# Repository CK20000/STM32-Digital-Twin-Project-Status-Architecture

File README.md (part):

# KiCAD PCB Digital Twin - Plugin — Project Status & Architecture

https://github.com/user-attachments/assets/57d7ef48-a6f0-49e4-94a5-dc855cec5e4c

---

## PROJECT OVERVIEW

for easy managing I have organized the source files, but if you ever want to run this exact example versions, you need to have all the files in the root directory !!!

A closed-loop digital twin that bridges:

- KiCad PCB design       -> hardware definition (topology + geometry + values)
- STM32F407VETx firmware -> control logic (compiled to .elf)
- Renode                 -> cycle-accurate virtual MCU execution
- Python + ZeroMQ        -> message-passing middleware
- ngspice                -> real analog circuit simulation (auto-generated)
- PyQt6 control panel    -> live external analog + digital input injection
- PyQt6 unified UI       -> all 7 viewers + control panel + pipeline in one window
- matplotlib             -> live PCB visualization with physics overlays

**Key achievement:** Zero hardcoded circuit knowledge, zero faked inputs.
Every number on screen traces from a real KiCad component through real
firmware through real SPICE. Every panel input travels through Renode's
memory bus and into the SPICE netlist, exactly like a real external signal.

https://github.com/user-attachments/assets/5415f41c-1950-47eb-a591-bcc1c15813ef

https://github.com/user-attachments/assets/28cafe8e-76d3-48ea-92d0-15f687ff5b82

https://github.com/user-attachments/assets/54334765-b6d6-46bb-97e2-3d35a90c9ced

https://github.com/user-attachments/assets/97b0375e-3175-4ab2-a4fb-0aa53eb2be76

https://github.com/user-attachments/assets/55057f72-92d3-42ab-a68e-e2e90e522510

Full data path:

```text
KiCad (.kicad_pcb) --+-- digital_twin_netlist.json  (electrical topology)
                     |
                     +-- pcb_geometry.json          (visual geometry)
                     |
                     v
                netlist_analyzer.py  --> component_classification.json
                     |
                     v
                spice_compiler.py    --> auto_generated.cir
                                         + source_metadata.json
                     |
                     v
                inject_trace_resistance.py
                     |
                     v
                auto_generated_with_traces.cir

STM32 Firmware (C) --> automation_plc.elf
                            |
                    Renode (virtual STM32F407)
                            |
                    +-------+--------+
                    |                |
              monitor tcp:1234   UARTs tcp:12345/12346
                    |                |
                    v                v
        renode_reader.py       stm32_bridge.py
        (owns monitor)         (RS485 + ESP)
                    |                |
        ZMQ PUB:5557 (OBS)      ZMQ PUB:5555
        ZMQ SUB:5558 (INJECT)       |
                    |               v
                    |          test_sub.py
                    |
        +-----------+--------------+
        |                          |
        v                          v
pyspice_solver.py            pyqt6_control.py
(OBS:5557 in)                (INJECT:5558 out)
(replaces V_* values)        (8 analog sliders)
        |                    (8 digital checkboxes)
        |                          |
   auto_generated_with_traces.cir |
        |                          |
   ngspice subprocess <------------+
        |
   ZMQ PUB:5556
   (SIM / RAIL / RAIL_I / POWER / CURRENT / LOAD_I / LED_I / PIN / NODE / DOUT)
        |
        +---------+---------+---------+---------+---------+---------+
        |         |         |         |         |         |         |
        v         v         v         v         v         v         v
    pcb_      pcb_      pcb_      pcb_      pcb_      pcb_      board_
    viewer    resist    current   voltage   heat      thermal   thermal
    (LEDs)    (R)       (I)       (V)       (P)       (Tj)      field_v2
```

## GOAL TRACKER

| #  | Goal                                                       | Status   |
|----|------------------------------------------------------------|----------|
| 1  | Live PCB overlay with animated LED states                  | DONE     |
| 2A | Trace resistance extraction + physics modeling             | DONE     |
| 2B | Current flow visualization on traces                       | DONE     |
| 2C | Power dissipation heat map (per component)                 | DONE     |
| 2D | Thermal simulation — per-component θja + 2D diffusion field| DONE     |
| 3  | Board health pre-check (rails, loads, overtemperature)     | DONE     |
| -- | Auto-generated SPICE compiler (unplanned bonus)            | DONE     |
| -- | Trace resistance injected into SPICE netlist               | DONE     |
| -- | Auto-generated source metadata (no hardcoded nets)         | DONE     |
| -- | Renode memory reader (replaces UART as firmware source)    | DONE     |
| -- | Bidirectional Python → Renode injection                    | DONE     |
| -- | External analog input control panel (PyQt6)                | DONE     |
| -- | External digital input control panel (PyQt6)               | DONE     |
| -- | Voltage viewer (per-net DC node voltages)                  | DONE     |
| -- | Digital-output "armed" state outline on current viewer     | DONE     |
| -- | Unified PyQt6 dashboard (tabs + sidebar + pipeline grid)   | DONE     |

---

## WHAT HAS BEEN ACHIEVED

### Foundation Layer

| Milestone                                                     | Status | Verified By                     |
|---------------------------------------------------------------|--------|---------------------------------|
| Hardware schematic review (ESP-12F, MAX3485, LM358, etc.)     | Done   | Netlist inspection              |
| KiCad PCB netlist extraction to JSON                          | Done   | extraction.py                   |
| STM32CubeMX pinout configured for all peripherals             | Done   | .ioc file, CubeMX GUI           |
| ADC1 with DMA (8 channels, circular mode)                     | Done   | adc.c generated                 |
| TIM4 PWM (4 motor channels on PD12-PD15)                      | Done   | tim.c generated                 |
| USB OTG FS Device CDC                                         | Done   | usb_device.c generated          |
| Firmware compiled to automation_plc.elf                       | Done   | STM32CubeIDE build              |
| Renode virtual STM32F407 running firmware                     | Done   | plc_twin machine started        |
| UARTs exposed as TCP sockets                                  | Done   | Ports 12345, 12346              |
| Renode monitor exposed on TCP 1234                            | Done   | renode_reader.py                |
| Python bridge (UART -> ZeroMQ) with byte-level framing        | Done   | Live PLC_ALIVE packets          |
| Subscriber displaying live ADC values                         | Done   | Parsed 8-channel ADC arrays     |
| End-to-end pipeline running continuously                      | Done   | 190000+ packets streamed        |

### Firmware Observable Layer

| Milestone                                                     | Status | Verified By                     |
|---------------------------------------------------------------|--------|---------------------------------|
| get_symbols.py parses linker .map for `obs_*`/`in_*` symbols  | Done   | symbols.json                    |
| renode_reader.py owns Renode monitor (single client on 1234)  | Done   | Live OBS stream                 |
| Batched contiguous-span read (1 monitor cmd per cycle)        | Done   | Fast polling                    |
| Publishes OBS:<name>:<hex> on ZMQ 5557                        | Done   | Subscribed by solver + panel    |
| Subscribes INJECT:<name>:<value> on ZMQ 5558                  | Done   | Writes via sysbus WriteWord     |
| Coalesces rapid injections (latest value wins per cycle)      | Done   | Slider drags don't flood        |
| Skips no-op writes (last_written cache)                       | Done   | Monitor stays clean             |
| Auto-reconnect on Renode monitor drop                         | Done   | Recovers from Renode restart    |
| renode_cmd.py one-shot monitor command tool                   | Done   | Manual debugging                |
| Digital inputs IE8..IE15 injectable via INJECT path            | Done   | 5000 mV → 5 V field voltage      |
| Digital outputs E0..E7, D12..D15 exposed for state display     | Done   | DOUT topic on ZMQ 5556           |

### Simulation Layer

| Milestone                                                     | Status | Verified By                     |
|---------------------------------------------------------------|--------|---------------------------------|
| Netlist analyzer — auto-classifies 143 components             | Done   | netlist_analyzer.py             |
| SPICE compiler — auto-generates netlist from KiCad data       | Done   | spice_compiler.py               |
| Source metadata emitter (SPICE branch <-> KiCad net)          | Done   | source_metadata.json            |
| STM32 self-load (50 mA) + ESP-12F load (80 mA) modeled        | Done   | Verified in ngspice output      |
| LDO + buck regulator models with upstream current reflection  | Done   | Voltage rails consistent        |
| Trace resistance (I²R losses over copper)                     | Done   | trace_resistance.py             |
| Trace resistance injected into SPICE between pads             | Done   | auto_generated_with_traces.cir  |
| Per-component SPICE power parsing (R, I, D elements)          | Done   | ngspice POWER topic             |
| Per-resistor current parsing (R_pd_E8..E15 pin currents)      | Done   | CURRENT:E8..E15 topic           |
| Behavioral optocoupler models (PC817, 6N137)                  | Done   | optocoupler.lib                 |
| Live solver with per-packet netlist rewriting                 | Done   | pyspice_solver.py               |
| OBS-driven value substitution (no UART dependency)            | Done   | Solved from renode_reader       |
| Per-net node voltages published as NODE:<net>:<volts>         | Done   | Voltage viewer                  |
| Digital-output state published as DOUT:<net>:<0/1>            | Done   | Current viewer "armed" outline  |

### External Control Layer

| Milestone                                                     | Status | Verified By                     |
|---------------------------------------------------------------|--------|---------------------------------|
| channels.json maps user channels → in_* → obs_*               | Done   | 8 analog + 8 digital entries    |
| pyqt6_control.py — analog sliders (0–10 V, 20 Hz flush)       | Done   | Verified live                   |
| pyqt6_control.py — digital checkboxes (IE8..IE15, 5 V ON)     | Done   | Verified live                   |
| Reads OBS back into panel to confirm injection landed         | Done   | obs label updates on slider move|
| input_injector.py — standalone CLI injector                   | Done   | Reference tool                  |
| Digital input: opto LED current ~10.6 mA when ON              | Done   | CURRENT:/f4/IO/IExx             |
| Digital input: MCU pin current ~0.33 mA through pull-down     | Done   | CURRENT:Exx                     |
| Upstream LDO reflects opto output load (~1.4 mA on 3v3-LDO1)  | Done   | RAIL_I:3v3-LDO1                 |
| Panel embedded into unified dashboard sidebar (live)          | Done   | No changes to pyqt6_control.py  |

### Visualization Layer

| Milestone                                                     | Status | Verified By                     |
|---------------------------------------------------------------|--------|---------------------------------|
| Automated PCB top-view renderer (no manual export)            | Done   | pcb_render.py                   |
| Copper trace + pad + body + silkscreen extraction             | Done   | pcb_geometry.json               |
| Rotation-aware pad rendering (fixes QFP at 45°)               | Done   | U5 verified                     |
| F.Fab chain-lines-to-polygon for component bodies             | Done   | All passives render correctly   |
| Performance optimization (PatchCollection / LineCollection)   | Done   | ~1700 artists → ~10 artists     |
| Live LED overlay (7 LEDs: D3-D9)                              | Done   | pcb_viewer.py                   |
| Trace resistance view with hover inspect                      | Done   | pcb_resistance_view.py          |
| Current flow view (colored traces on top layer)               | Done   | pcb_current_view.py             |
| Power dissipation heat map (log + linear + jet)               | Done   | pcb_heat_view.py                |
| Per-component thermal view (θja model)                        | Done   | pcb_thermal_view.py             |
| 2D thermal field v1 (single-layer k_eff)                      | Done   | pcb_thermal_field.py            |
| 2D thermal field v2 (2-layer copper + vias + FR4)             | Done   | pcb_thermal_field_v2.py         |
| Bounding-box hover detection for large components             | Done   | Fixed for U4/U5                 |
| Voltage view (per-net DC voltage, viridis 0–12 V)             | Done   | pcb_voltage_view.py             |
| Digital-output outline (amber=ARMED, slate=IDLE)              | Done   | pcb_current_view.py             |
| Resistance viewer info panel visible at startup               | Done   | pcb_resistance_view.py          |
| Unified dashboard — 7 tabs + sidebar + pipeline grid          | Done   | dashboard_unified.py            |

### Automation Layer (Goal 3)

| Milestone                                                     | Status | Verified By                     |
|---------------------------------------------------------------|--------|---------------------------------|
| Board health monitor (12-test battery)                        | Done   | board_health.py                 |
| Rail voltage tolerance check (±5%)                            | Done   | All 4 rails PASS                |
| Load current plausibility check                               | Done   | STM32 + ESP PASS                |
| Total power budget check                                      | Done   | <2 W threshold                  |
| Over-temperature prediction (θja model)                       | Done   | Peak 38.1 °C at U4              |
| Short-circuit detection (rail current > 1 A)                  | Done   | Max 144.7 mA                    |
| SIM packet freshness check                                    | Done   | <5 s stale threshold            |
| ADC channel-set verification                                  | Done   | 4/4 SIM fields present          |
| ESP packet rate monitor (rolling window)                      | Done   | 4-6 Hz observed                 |
| Single-shot mode with exit code (`--once`)                    | Done   | CI-friendly                     |

---

## PROJECT FILE INVENTORY

### Core Pipeline Files

| File                | Language      | Purpose                                                                  |
|---------------------|---------------|--------------------------------------------------------------------------|
| run_core.bat        | Batch         | Pre-flight + launches Renode, bridge, reader, solver, subscriber        |
| run_unified_dashboard.bat | Batch   | Launches the unified dashboard; pipeline starts inside as tabs          |
| run_led_viewer.bat  | Batch         | Opens pcb_viewer.py                                                     |
| run_current_viewer.bat | Batch      | Opens pcb_current_view.py                                               |
| run_voltage_viewer.bat | Batch    | Opens pcb_voltage_view.py standalone                                     |
| run_resistance_viewer.bat | Batch    | Opens pcb_resistance_view.py                                            |
| run_heat_viewer.bat | Batch         | Opens pcb_heat_view.py                                                  |
| run_thermal_viewer.bat | Batch      | Opens pcb_thermal_field_v2.py                                           |
| run_health.bat      | Batch         | Continuous health monitor                                               |
| run_health_once.bat | Batch         | Single-shot health check with exit code                                 |
| rebuild_spice.bat   | Batch         | Regenerates classification → SPICE → trace injection                    |
| rebuild_geometry.bat| Batch         | Two-step geometry regeneration (KiCad Python + system Python)           |
| stop_all.bat        | Batch         | Kills Renode, ngspice, and project Python processes                     |
| machine.resc        | Renode script | Defines virtual STM32F407, loads .elf, exposes UARTs                    |
| stm32_bridge.py     | Python        | Reads TCP UART streams, publishes RS485/ESP to ZMQ 5555                 |
| renode_reader.py    | Python        | Owns Renode monitor 1234, reads obs_*, writes in_*, ZMQ 5557/5558       |
| get_symbols.py      | Python        | Parses linker .map → symbols.json (obs_* and in_* addresses)            |
| input_injector.py   | Python        | Standalone INJECT publisher (reference tool)                            |
| renode_cmd.py       | Python        | One-shot Renode monitor command tool                                    |
| pyspice_solver.py   | Python        | Loads netlist, substitutes OBS values, calls ngspice, publishes 5556    |
| pyqt6_control.py    | Python        | External control panel (8 analog sliders + 8 digital checkboxes)        |
| dashboard_unified.py| Python        | All-in-one PyQt6 dashboard (7 viewer tabs + sidebar + pipeline grid)     |
| test_sub.py         | Python        | Subscribes to all ZMQ topics and displays live text data                |

### Auto-SPICE Compiler Files

| File                            | Purpose                                                        |
|---------------------------------|----------------------------------------------------------------|
| netlist_analyzer.py             | Classifies every component (R, C, LED, LDO, MCU, etc.)         |
| component_classification.json   | Output: type + value + nets per refdes                         |
| spice_compiler.py               | Generates complete SPICE netlist + source metadata             |
| auto_generated.cir              | Generated SPICE netlist (143 components + rails + loads)       |
| source_metadata.json            | Maps SPICE branch names to KiCad nets (no hardcoding)          |
| inject_trace_resistance.py      | Injects R_trace elements between regulator and load            |
| auto_generated_with_traces.cir  | Final netlist — this is what the solver loads                  |
| optocoupler.lib                 | Behavioral SPICE subcircuits for PC817 and 6N137               |

### Hardware / Physics Files

| File                          | Purpose                                                       |
|-------------------------------|---------------------------------------------------------------|
| automation.kicad_pcb          | KiCad PCB layout (source of truth)                            |
| automation.kicad_pro          | KiCad project file                                            |
| automation.kicad_sch          | KiCad main schematic                                          |
| A_IN.kicad_sch                | Analog input schematic sheet                                  |
| IO.kicad_sch                  | Industrial I/O schematic sheet                                |
| MOTORS.kicad_sch              | Motor driver schematic sheet                                  |
| DEBUG.kicad_sch               | Debug/LED schematic sheet                                     |
| f4.kicad_sch                  | STM32F407 core schematic sheet                                |
| digital_twin_netlist.json     | Extracted net topology (component, value, pin, net)           |
| extraction.py                 | pcbnew script that generates the JSON netlist from the PCB    |
| trace_resistance.py           | Computes DC resistance per trace + per net                    |
| net_resistance.json           | Output: resistance topology                                   |
| automation_plc.ioc            | STM32CubeMX project configuration                             |

### Visualization Files

| File                     | Language  | Purpose                                                              |
|--------------------------|-----------|----------------------------------------------------------------------|
| pcb_extract_geometry.py  | Python    | Reads .kicad_pcb via pcbnew, dumps geometry to JSON                  |
| pcb_geometry.json        | JSON      | Tracks, vias, footprints, pads, F.Fab, F.SilkS                       |
| pcb_render.py            | Python    | Renders pcb_background.png                                           |
| pcb_render_meta.json     | JSON      | Pixel <-> mm coordinate mapping                                      |
| pcb_background.png       | PNG       | Static PCB top-view render                                           |
| pcb_viewer.py            | Python    | Live LED overlay (Goal 1)                                            |
| pcb_resistance_view.py   | Python    | Trace resistance view with hover                                     |
| pcb_current_view.py      | Python    | Current flow view (colored traces on top)                            |
| pcb_voltage_view.py      | Python    | Per-net DC voltage view (live from ngspice NODE topic)               |
| pcb_heat_view.py         | Python    | Power dissipation heat map                                           |
| pcb_thermal_view.py      | Python    | Per-component θja thermal view                                       |
| pcb_thermal_field.py     | Python    | 2D thermal diffusion (single-layer k_eff)                            |
| pcb_thermal_field_v2.py  | Python    | 2D thermal diffusion (2-layer copper + vias + FR4)                   |

### Configuration Files

| File              | Purpose                                                       |
|-------------------|---------------------------------------------------------------|
| channels.json     | Channel map: id → in_* symbol → obs_* observable → kind       |
| symbols.json      | Address + size of every obs_* and in_* firmware variable      |

### Automation Files

| File              | Purpose                                                    |
|-------------------|------------------------------------------------------------|
| board_health.py   | 12-test battery, continuous or --once mode                 |

### Firmware Files

| File                                 | Purpose                                              |
|--------------------------------------|------------------------------------------------------|
| firmware/Debug/automation_plc.elf    | Compiled firmware (used by Renode)                   |
| firmware/Core/Src/main.c             | Main application (injection copy loop + LED bitmask) |
| firmware/Core/Src/adc.c              | ADC1 + DMA initialization                            |
| firmware/Core/Src/dac.c              | DAC1/DAC2 initialization                             |
| firmware/Core/Src/tim.c              | TIM4 PWM initialization                              |
| firmware/Core/Src/usart.c            | USART2, USART3 initialization                        |
| firmware/Core/Src/spi.c              | SPI1, SPI2 initialization                            |
| firmware/Core/Src/i2c.c              | I2C1 initialization                                  |
| firmware/Core/Src/gpio.c             | GPIO init                                            |
| firmware/Core/Src/dma.c              | DMA controller initialization                        |
| firmware/Core/Src/usb_device.c       | USB CDC device setup                                 |
| firmware/automation_plc.ioc          | CubeMX project (used for regeneration)               |

### External Dependencies

| Dependency     | Version    | Purpose                                                              |
|----------------|------------|----------------------------------------------------------------------|
| STM32CubeMX    | (latest)   | Pin/peripheral configurator                                          |
| STM32CubeIDE   | (latest)   | Compiler + debugger                                                  |
| Renode         | (latest)   | Virtual MCU execution                                                |
| ngspice        | 47         | Analog circuit simulator (C:\Users\user\Downloads\Spice64\bin\ngspice_con.exe) |
| Python (system)| 3.10+      | All pipeline scripts + viewers                                       |
| Python (KiCad) | 3.x        | Only used for pcbnew scripts (extraction)                            |
| pyzmq          | latest     | ZeroMQ bindings                                                      |
| matplotlib     | latest     | All rendering + live viewers                                         |
| scipy          | latest     | Sparse solver for 2D thermal diffusion                               |
| PyQt6          | latest     | External control panel GUI + unified dashboard                       |

---

## STM32F407VETx PINOUT (FINAL)

| Peripheral              | Pin                | Function                    | Notes                          |
|-------------------------|--------------------|-----------------------------|--------------------------------|
| HSE Crystal             | PH0, PH1           | RCC_OSC_IN/OUT              | 8 MHz                          |
| Debug                   | PA13, PA14         | SWDIO, SWCLK                | Serial Wire mode               |
| ESP-12F                 | PB10, PB11         | USART3_TX/RX                | 115200 8N1                     |
| MAX3485 (RS-485)        | PA2, PA3, PD11     | USART2_TX/RX, DE/RE         | Direction control on PD11      |
| W25Q128 (SPI Flash)     | PB3, PB4, PB5, PD6 | SPI1_SCK/MISO/MOSI, CS      | CS on PD6                      |
| USB-C                   | PA11, PA12         | USB_DM, USB_DP              | Full Speed Device              |
| Motor PWM               | PD12-PD15          | TIM4_CH1-CH4                | 4 channels                     |
| Debug LEDs              | PC10, PC11, PC12, PA15 | GPIO_Output             |                                |
| I2C Expansion           | PB6, PB7           | I2C1_SCL/SDA                |                                |
| Analog In 1-4           | PC0-PC3            | ADC1_IN10-13                | 0-10V via 10k/4.7k divider     |
| Analog In 5-6           | PC4, PC5           | ADC1_IN14-15                | Same divider                   |
| Analog In 7-8           | PB0, PB1           | ADC1_IN8-9                  | Same divider                   |
| Analog Out 1-2          | PA4, PA5           | DAC_OUT1/2                  | Via LM358 gain=3               |
| Digital Inputs 8-15     | PE8-PE15           | GPIO_Input                  | Opto-isolated (U31..U30)       |

ADC Rank Ordering (as configured in CubeMX):

    Rank 1: IN8  (PB0) -> adc_values[0]  -> A_IN7
    Rank 2: IN9  (PB1) -> adc_values[1]  -> A_IN8
    Rank 3: IN10 (PC0) -> adc_values[2]  -> A_IN1
    Rank 4: IN11 (PC1) -> adc_values[3]  -> A_IN2
    Rank 5: IN12 (PC2) -> adc_values[4]  -> A_IN3
    Rank 6: IN13 (PC3) -> adc_values[5]  -> A_IN4
    Rank 7: IN14 (PC4) -> adc_values[6]  -> A_IN5
    Rank 8: IN15 (PC5) -> adc_values[7]  -> A_IN6

---

## DATA PROTOCOLS

### Renode Observable Protocol (Renode → Python)

`renode_reader.py` reads a single contiguous span containing every
`obs_*` / `in_*` symbol and publishes each one:

    OBS:<symbol_name>:<hex_bytes>

Example:

    OBS:obs_v_in1:7f0f
    OBS:obs_v_ie8_drv:8813
    OBS:obs_v_d4_drv:00

Published on ZMQ **5557**.

### Renode Injection Protocol (Python → Renode)

Any subscriber publishes:

    INJECT:<symbol_name>:<uint16_value>

Example:

    INJECT:in_v_in1:3967
    INJECT:in_v_ie8_drv:5000

Published on ZMQ **5558**; `renode_reader.py` coalesces and writes via
`sysbus WriteWord` to the symbol's address.

### ESP UART Packet (Firmware → Bridge, legacy path)

- 20 bytes total
- [0xAA][0x55] — sync header
- 8 × 16-bit big-endian ADC values (bytes 2-17)
- 1 byte LED bitmask (byte 18)
- 1 byte reserved (byte 19)

### ZeroMQ Topics

| Topic                        | Port | Publisher      | Format                                    |
|------------------------------|------|----------------|-------------------------------------------|
| RS485:<hex>                  | 5555 | stm32_bridge   | Hex-encoded ASCII ("PLC_ALIVE\r\n")       |
| ESP:<hex>                    | 5555 | stm32_bridge   | Hex-encoded 20-byte ADC + LED packet      |
| OBS:<name>:<hex>             | 5557 | renode_reader  | Firmware observable raw bytes             |
| INJECT:<name>:<value>        | 5558 | any            | Write request to a firmware variable      |
| SIM:<n>:<key=val,...>        | 5556 | solver         | Simulation summary string                 |
| CURRENT:<net>:<amps>         | 5556 | solver         | Per-net current (auto-mapped + pin R's)   |
| POWER:<ref>:<watts>          | 5556 | solver         | Per-component power dissipation           |
| RAIL:<net>:<volts>           | 5556 | solver         | Power rail node voltages                  |
| RAIL_I:<net>:<amps>          | 5556 | solver         | Power rail delivered currents             |
| LED_I:<ref>:<amps>           | 5556 | solver         | LED drive currents                        |
| LOAD_I:<label>:<amps>        | 5556 | solver         | MCU / ESP self-load currents              |
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
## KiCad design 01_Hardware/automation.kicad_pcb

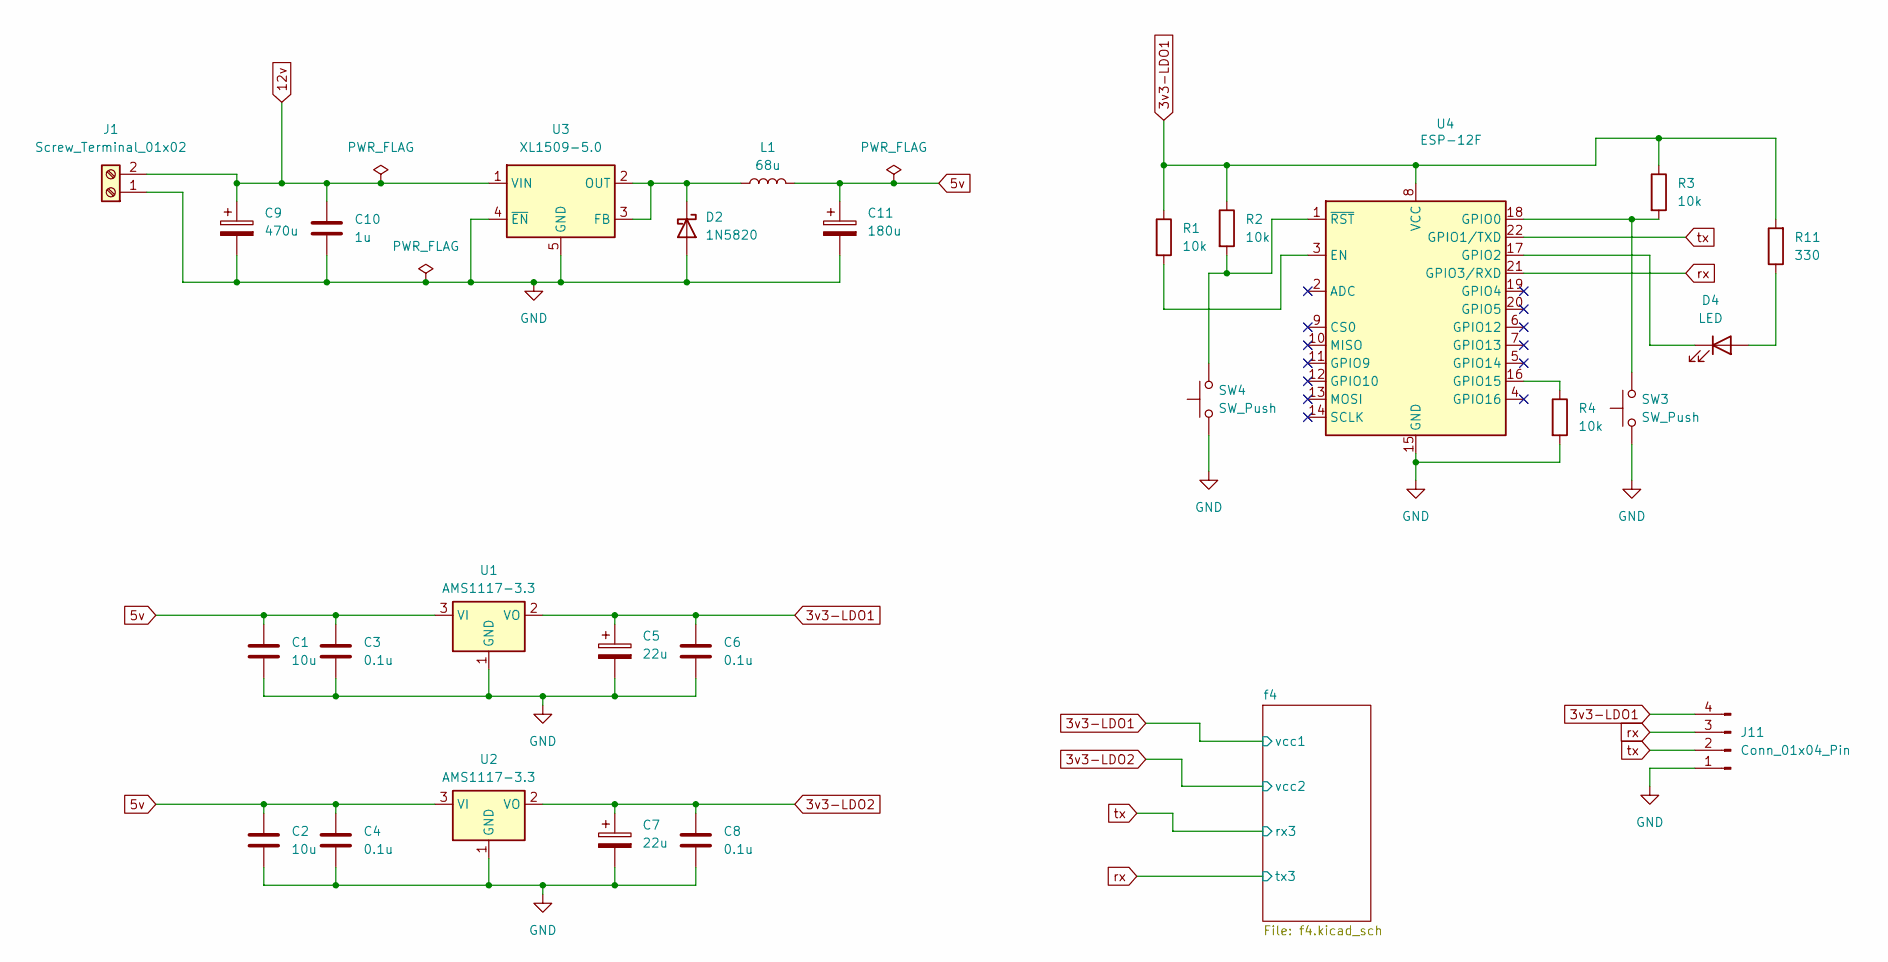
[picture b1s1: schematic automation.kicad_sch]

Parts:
C1, C2: 10u; C_0805_2012Metric_Pad1.18x1.45mm_HandSolder
C3, C4, C6, C8: 0.1u; C_0805_2012Metric_Pad1.18x1.45mm_HandSolder
C5, C7: 22u; C_0805_2012Metric_Pad1.18x1.45mm_HandSolder
C9: 470u; C_0805_2012Metric_Pad1.18x1.45mm_HandSolder
C10: 1u; C_0805_2012Metric_Pad1.18x1.45mm_HandSolder
C11: 180u; C_0805_2012Metric_Pad1.18x1.45mm_HandSolder
D2: 1N5820; D_1206_3216Metric_Pad1.42x1.75mm_HandSolder
D4: LED; LED_0805_2012Metric_Pad1.15x1.40mm_HandSolder
J1: Screw_Terminal_01x02; TerminalBlock_Phoenix_MKDS-1,5-2_1x02_P5.00mm_Horizontal
J11: Conn_01x04_Pin; PinHeader_1x04_P2.54mm_Vertical
L1: 68u; L_APV_ANR6020
R1, R2, R3, R4: 10k; R_0805_2012Metric_Pad1.20x1.40mm_HandSolder
R11: 330; R_0805_2012Metric_Pad1.20x1.40mm_HandSolder
SW3, SW4: SW_Push; SW_Push_SPST_NO_Alps_SKRK
U1, U2: AMS1117-3.3; SOT-223-3_TabPin2
U3: XL1509-5.0; SOIC-8_3.9x4.9mm_P1.27mm
U4: ESP-12F; ESP-12E

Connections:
3v3-LDO1: C5.1, C6.1, J11.4, R1.1, R2.1, R3.1, R11.2, U1.2 (VO), U4.8 (VCC); also elsewhere on the board
3v3-LDO2: C7.1, C8.1, U2.2 (VO); also elsewhere on the board
5v: C1.1, C2.1, C3.1, C4.1, C11.1, L1.2, U1.3 (VI), U2.3 (VI); also elsewhere on the board
12v: C9.1, C10.1, J1.2, U3.1 (VIN); also elsewhere on the board
GND: C1.2, C2.2, C3.2, C4.2, C5.2, C6.2, C7.2, C8.2, C9.2, C10.2, C11.2, D2.2 (A), J1.1, J11.1, R4.2, SW3.1, SW4.1, U1.1 (GND), U2.1 (GND), U3.4 (~EN), U3.5 (GND), U3.6 (GND), U3.7 (GND), U3.8 (GND), U4.15 (GND); also elsewhere on the board
unnamed: D2.1 (K), L1.1, U3.2 (OUT), U3.3 (FB)
unnamed: D4.2 (A), R11.1
unnamed: D4.1 (K), U4.17 (GPIO2)
unnamed: R1.2, U4.3 (EN)
unnamed: R3.2, SW3.2, U4.18 (GPIO0)
unnamed: R4.1, U4.16 (GPIO15)
unnamed: R2.2, SW4.2, U4.1 (~RST)
rx: J11.3, U4.21 (GPIO3/RXD); also elsewhere on the board
tx: J11.2, U4.22 (GPIO1/TXD); also elsewhere on the board

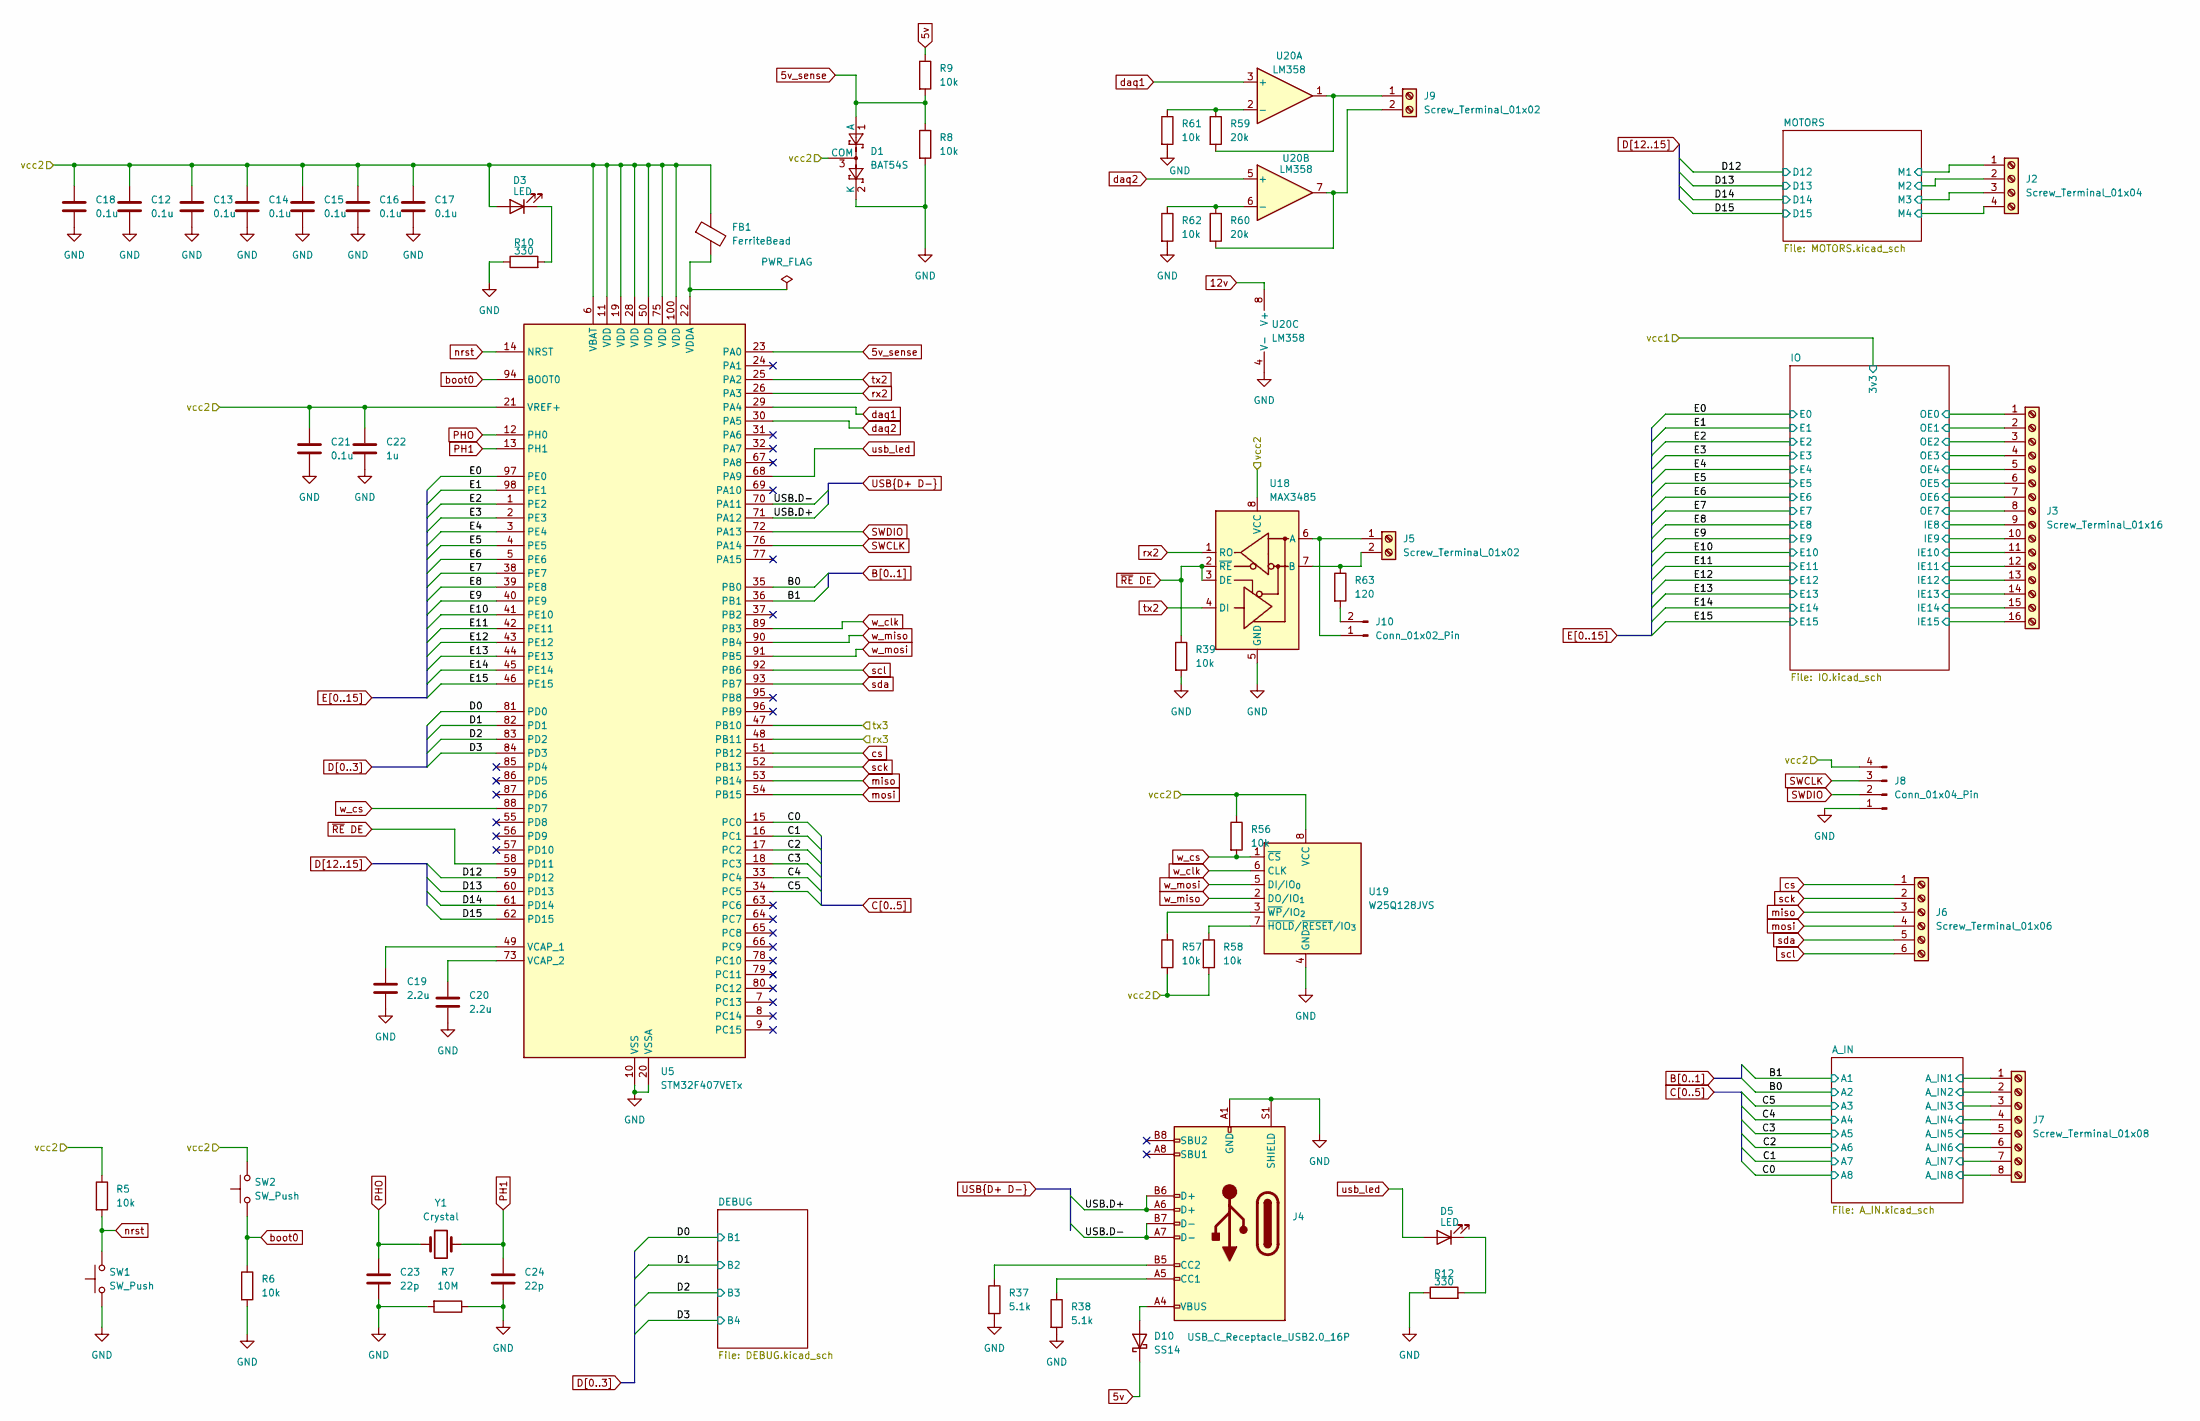
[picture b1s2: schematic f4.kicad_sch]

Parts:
C12, C13, C14, C15, C16, C17, C18, C21: 0.1u; C_0805_2012Metric_Pad1.18x1.45mm_HandSolder
C19, C20: 2.2u; C_0805_2012Metric_Pad1.18x1.45mm_HandSolder
C22: 1u; C_0805_2012Metric_Pad1.18x1.45mm_HandSolder
C23, C24: 22p; C_0805_2012Metric_Pad1.18x1.45mm_HandSolder
D1: BAT54S; SOT-23
D3, D5: LED; LED_0805_2012Metric_Pad1.15x1.40mm_HandSolder
D10: SS14; D_SMA
FB1: FerriteBead; L_1206_3216Metric_Pad1.22x1.90mm_HandSolder
J2: Screw_Terminal_01x04; TerminalBlock_Phoenix_MKDS-1,5-4_1x04_P5.00mm_Horizontal
J3: Screw_Terminal_01x16; TerminalBlock_Phoenix_MKDS-1,5-16_1x16_P5.00mm_Horizontal
J4: USB_C_Receptacle_USB2.0_16P; USB_C_Receptacle_GCT_USB4105-xx-A_16P_TopMnt_Horizontal
J5, J9: Screw_Terminal_01x02; TerminalBlock_Phoenix_MKDS-1,5-2_1x02_P5.00mm_Horizontal
J6: Screw_Terminal_01x06; TerminalBlock_Phoenix_MKDS-1,5-6_1x06_P5.00mm_Horizontal
J7: Screw_Terminal_01x08; TerminalBlock_Phoenix_MKDS-1,5-8_1x08_P5.00mm_Horizontal
J8: Conn_01x04_Pin; PinHeader_1x04_P2.54mm_Vertical
J10: Conn_01x02_Pin; PinHeader_1x02_P2.54mm_Vertical
R5, R6, R8, R9, R39, R56, R57, R58, R61, R62: 10k; R_0805_2012Metric_Pad1.20x1.40mm_HandSolder
R7: 10M; R_0805_2012Metric_Pad1.20x1.40mm_HandSolder
R10, R12: 330; R_0805_2012Metric_Pad1.20x1.40mm_HandSolder
R37, R38: 5.1k; R_0805_2012Metric_Pad1.20x1.40mm_HandSolder
R59, R60: 20k; R_0805_2012Metric_Pad1.20x1.40mm_HandSolder
R63: 120; R_0805_2012Metric_Pad1.20x1.40mm_HandSolder
SW1, SW2: SW_Push; SW_Push_SPST_NO_Alps_SKRK
U5: STM32F407VETx; LQFP-100_14x14mm_P0.5mm
U18: MAX3485; SOIC-8_3.9x4.9mm_P1.27mm
U19: W25Q128JVS; SOIC-8_5.3x5.3mm_P1.27mm
U20: LM358; SOIC-8_3.9x4.9mm_P1.27mm
Y1: Crystal; Crystal_HC52-6mm_Vertical

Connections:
3v3-LDO2: C12.1, C13.1, C14.1, C15.1, C16.1, C17.1, C18.1, C21.1, C22.1, D1.3 (COM), D3.2 (A), FB1.1, J8.4, R5.1, R56.1, R57.2, R58.2, SW2.2, U5.6 (VBAT), U5.11 (VDD), U5.19 (VDD), U5.21 (VREF+), U5.28 (VDD), U5.50 (VDD), U5.75 (VDD), U5.100 (VDD), U18.8 (VCC), U19.8 (VCC); also elsewhere on the board
5v: D10.1 (K), R9.1; also elsewhere on the board
5v_sense: D1.1 (A), R8.1, R9.2, U5.23 (PA0)
12v: U20.8 (V+); also elsewhere on the board
/f4/A_IN/A_IN1: J7.1; also elsewhere on the board
/f4/A_IN/A_IN2: J7.2; also elsewhere on the board
/f4/A_IN/A_IN3: J7.3; also elsewhere on the board
/f4/A_IN/A_IN4: J7.4; also elsewhere on the board
/f4/A_IN/A_IN5: J7.5; also elsewhere on the board
/f4/A_IN/A_IN6: J7.6; also elsewhere on the board
/f4/A_IN/A_IN7: J7.7; also elsewhere on the board
/f4/A_IN/A_IN8: J7.8; also elsewhere on the board
/f4/IO/IE8: J3.9; also elsewhere on the board
/f4/IO/IE9: J3.10; also elsewhere on the board
/f4/IO/IE10: J3.11; also elsewhere on the board
/f4/IO/IE11: J3.12; also elsewhere on the board
/f4/IO/IE12: J3.13; also elsewhere on the board
/f4/IO/IE13: J3.14; also elsewhere on the board
/f4/IO/IE14: J3.15; also elsewhere on the board
/f4/IO/IE15: J3.16; also elsewhere on the board
/f4/IO/OE0: J3.1; also elsewhere on the board
/f4/IO/OE1: J3.2; also elsewhere on the board
/f4/IO/OE2: J3.3; also elsewhere on the board
/f4/IO/OE3: J3.4; also elsewhere on the board
/f4/IO/OE4: J3.5; also elsewhere on the board
/f4/IO/OE5: J3.6; also elsewhere on the board
/f4/IO/OE6: J3.7; also elsewhere on the board
/f4/IO/OE7: J3.8; also elsewhere on the board
/f4/MOTORS/M1: J2.1; also elsewhere on the board
/f4/MOTORS/M2: J2.2; also elsewhere on the board
/f4/MOTORS/M3: J2.3; also elsewhere on the board
/f4/MOTORS/M4: J2.4; also elsewhere on the board
B0: U5.35 (PB0); also elsewhere on the board
B1: U5.36 (PB1); also elsewhere on the board
C0: U5.15 (PC0); also elsewhere on the board
C1: U5.16 (PC1); also elsewhere on the board
C2: U5.17 (PC2); also elsewhere on the board
C3: U5.18 (PC3); also elsewhere on the board
C4: U5.33 (PC4); also elsewhere on the board
C5: U5.34 (PC5); also elsewhere on the board
D0: U5.81 (PD0); also elsewhere on the board
D1: U5.82 (PD1); also elsewhere on the board
D2: U5.83 (PD2); also elsewhere on the board
D3: U5.84 (PD3); also elsewhere on the board
D12: U5.59 (PD12); also elsewhere on the board
D13: U5.60 (PD13); also elsewhere on the board
D14: U5.61 (PD14); also elsewhere on the board
D15: U5.62 (PD15); also elsewhere on the board
E0: U5.97 (PE0); also elsewhere on the board
E1: U5.98 (PE1); also elsewhere on the board
E2: U5.1 (PE2); also elsewhere on the board
E3: U5.2 (PE3); also elsewhere on the board
E4: U5.3 (PE4); also elsewhere on the board
E5: U5.4 (PE5); also elsewhere on the board
E6: U5.5 (PE6); also elsewhere on the board
E7: U5.38 (PE7); also elsewhere on the board
E8: U5.39 (PE8); also elsewhere on the board
E9: U5.40 (PE9); also elsewhere on the board
E10: U5.41 (PE10); also elsewhere on the board
E11: U5.42 (PE11); also elsewhere on the board
E12: U5.43 (PE12); also elsewhere on the board
E13: U5.44 (PE13); also elsewhere on the board
E14: U5.45 (PE14); also elsewhere on the board
E15: U5.46 (PE15); also elsewhere on the board
GND: C12.2, C13.2, C14.2, C15.2, C16.2, C17.2, C18.2, C19.2, C20.2, C21.2, C22.2, C23.2, C24.2, D1.2 (K), J4.A1 (GND), J4.A12 (GND), J4.B1 (GND), J4.B12 (GND), J4.S1 (SHIELD), J8.1, R6.2, R7.1, R7.2, R8.2, R10.1, R12.1, R37.2, R38.2, R39.2, R61.2, R62.2, SW1.1, U5.10 (VSS), U5.20 (VSSA), U5.27 (VSS), U5.74 (VSS), U5.99 (VSS), U18.5 (GND), U19.4 (GND), U20.4 (V-); also elsewhere on the board
unnamed: D3.1 (K), R10.2
unnamed: D5.1 (K), R12.2
unnamed: D10.2 (A), J4.A4 (VBUS), J4.A9 (VBUS), J4.B4 (VBUS), J4.B9 (VBUS)
unnamed: J4.A5 (CC1), R38.1
unnamed: J4.B5 (CC2), R37.1
unnamed: J5.2, R63.1, U18.7 (B)
unnamed: J9.1, R59.2, U20.1
unnamed: J9.2, R60.2, U20.7
unnamed: J5.1, J10.1, U18.6 (A)
unnamed: J10.2, R63.2
unnamed: C19.1, U5.49 (VCAP_1)
unnamed: C20.1, U5.73 (VCAP_2)
unnamed: FB1.2, U5.22 (VDDA)
unnamed: R58.1, U19.7 (~HOLD/~RESET/IO_{3})
unnamed: R57.1, U19.3 (~WP/IO_{2})
unnamed: R59.1, R61.1, U20.2 (-)
unnamed: R60.1, R62.1, U20.6 (-)
PH1: C24.1, U5.13 (PH1), Y1.2
PHO: C23.1, U5.12 (PH0), Y1.1
SWCLK: J8.3, U5.76 (PA14)
SWDIO: J8.2, U5.72 (PA13)
USB.D+: J4.A6 (D+), J4.B6 (D+), U5.71 (PA12)
USB.D-: J4.A7 (D-), J4.B7 (D-), U5.70 (PA11)
boot0: R6.1, SW2.1, U5.94 (BOOT0)
cs: J6.1, U5.51 (PB12)
daq1: U5.29 (PA4), U20.3 (+)
daq2: U5.30 (PA5), U20.5 (+)
miso: J6.3, U5.53 (PB14)
mosi: J6.4, U5.54 (PB15)
nrst: R5.2, SW1.2, U5.14 (NRST)
rx: U5.47 (PB10); also elsewhere on the board
rx2: U5.26 (PA3), U18.1 (RO)
sck: J6.2, U5.52 (PB13)
scl: J6.6, U5.92 (PB6)
sda: J6.5, U5.93 (PB7)
tx: U5.48 (PB11); also elsewhere on the board
tx2: U5.25 (PA2), U18.4 (DI)
usb_led: D5.2 (A), U5.68 (PA9)
w_clk: U5.89 (PB3), U19.6 (CLK)
w_cs: R56.2, U5.88 (PD7), U19.1 (~CS)
w_miso: U5.90 (PB4), U19.2 (DO/IO_{1})
w_mosi: U5.91 (PB5), U19.5 (DI/IO_{0})
~RE DE: R39.1, U5.58 (PD11), U18.2 (~RE), U18.3 (DE)

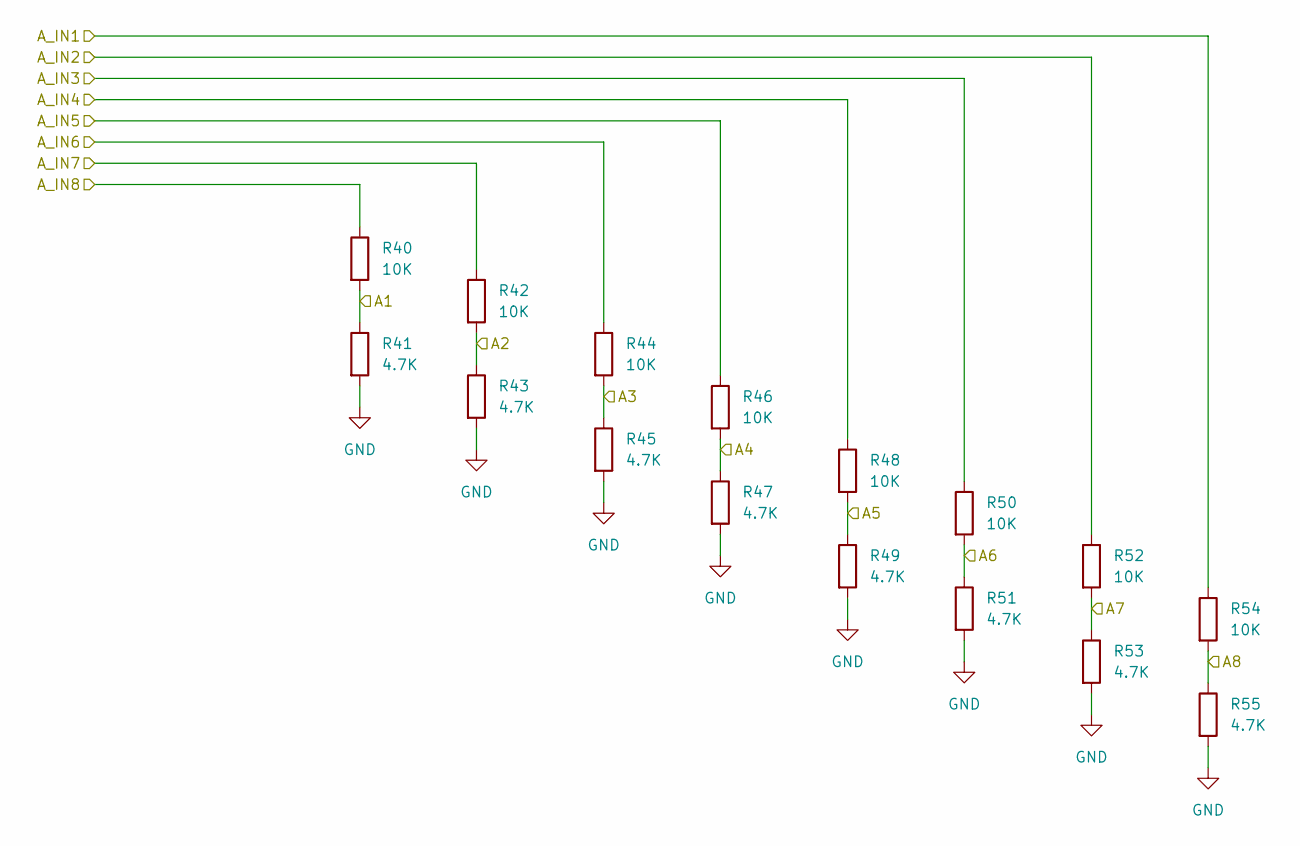
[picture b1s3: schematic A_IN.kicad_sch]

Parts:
R40, R42, R44, R46, R48, R50, R52, R54: 10K; R_0805_2012Metric_Pad1.20x1.40mm_HandSolder
R41, R43, R45, R47, R49, R51, R53, R55: 4.7K; R_0805_2012Metric_Pad1.20x1.40mm_HandSolder

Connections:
/f4/A_IN/A_IN1: R54.1; also elsewhere on the board
/f4/A_IN/A_IN2: R52.1; also elsewhere on the board
/f4/A_IN/A_IN3: R50.1; also elsewhere on the board
/f4/A_IN/A_IN4: R48.1; also elsewhere on the board
/f4/A_IN/A_IN5: R46.1; also elsewhere on the board
/f4/A_IN/A_IN6: R44.1; also elsewhere on the board
/f4/A_IN/A_IN7: R42.1; also elsewhere on the board
/f4/A_IN/A_IN8: R40.1; also elsewhere on the board
B0: R42.2, R43.1; also elsewhere on the board
B1: R40.2, R41.1; also elsewhere on the board
C0: R54.2, R55.1; also elsewhere on the board
C1: R52.2, R53.1; also elsewhere on the board
C2: R50.2, R51.1; also elsewhere on the board
C3: R48.2, R49.1; also elsewhere on the board
C4: R46.2, R47.1; also elsewhere on the board
C5: R44.2, R45.1; also elsewhere on the board
GND: R41.2, R43.2, R45.2, R47.2, R49.2, R51.2, R53.2, R55.2; also elsewhere on the board

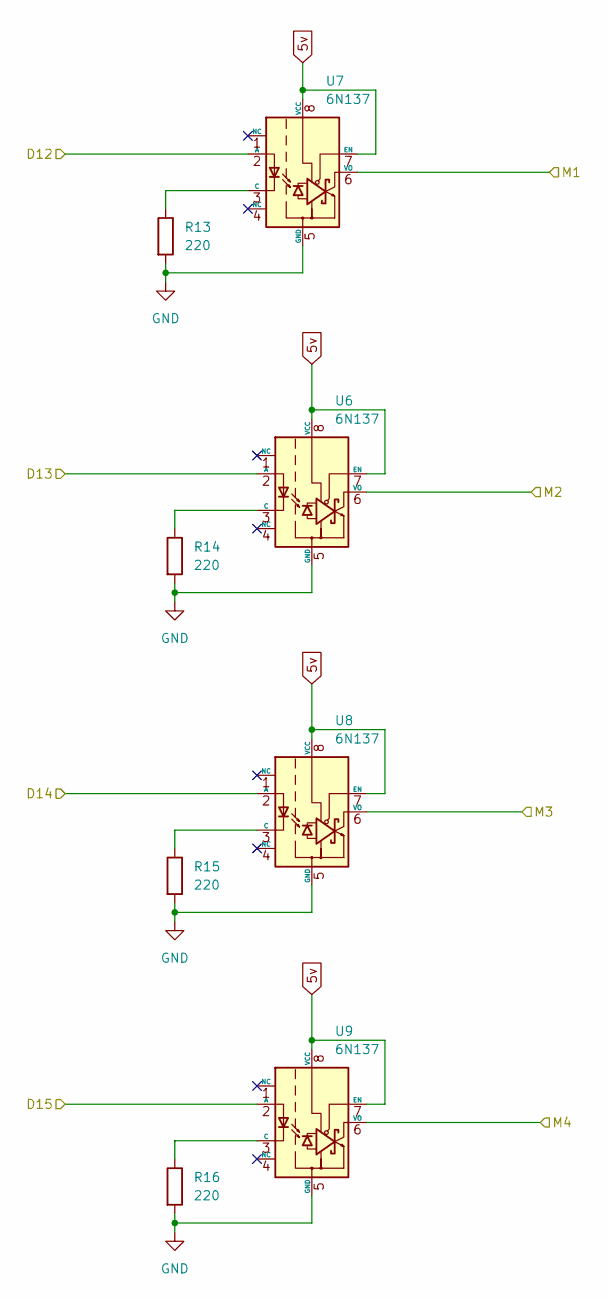
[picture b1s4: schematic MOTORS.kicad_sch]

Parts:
R13, R14, R15, R16: 220; R_0805_2012Metric_Pad1.20x1.40mm_HandSolder
U6, U7, U8, U9: 6N137; DIP-8_W7.62mm

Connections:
5v: U6.7 (EN), U6.8 (VCC), U7.7 (EN), U7.8 (VCC), U8.7 (EN), U8.8 (VCC), U9.7 (EN), U9.8 (VCC); also elsewhere on the board
/f4/MOTORS/M1: U7.6 (VO); also elsewhere on the board
/f4/MOTORS/M2: U6.6 (VO); also elsewhere on the board
/f4/MOTORS/M3: U8.6 (VO); also elsewhere on the board
/f4/MOTORS/M4: U9.6 (VO); also elsewhere on the board
D12: U7.2 (A); also elsewhere on the board
D13: U6.2 (A); also elsewhere on the board
D14: U8.2 (A); also elsewhere on the board
D15: U9.2 (A); also elsewhere on the board
GND: R13.2, R14.2, R15.2, R16.2, U6.5 (GND), U7.5 (GND), U8.5 (GND), U9.5 (GND); also elsewhere on the board
unnamed: R14.1, U6.3 (C)
unnamed: R13.1, U7.3 (C)
unnamed: R15.1, U8.3 (C)
unnamed: R16.1, U9.3 (C)

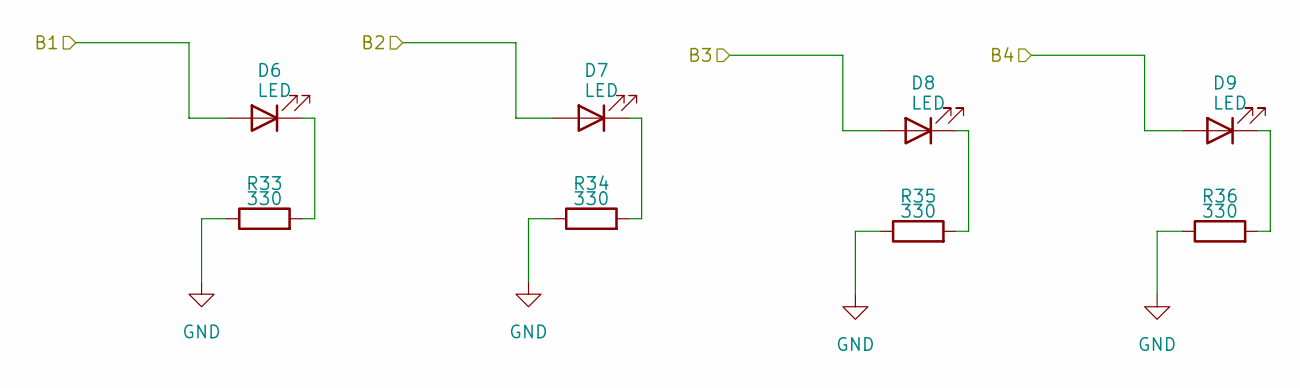
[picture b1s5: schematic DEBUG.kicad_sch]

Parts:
D6, D7, D8, D9: LED; LED_0805_2012Metric_Pad1.15x1.40mm_HandSolder
R33, R34, R35, R36: 330; R_0805_2012Metric_Pad1.20x1.40mm_HandSolder

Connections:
D0: D6.2 (A); also elsewhere on the board
D1: D7.2 (A); also elsewhere on the board
D2: D8.2 (A); also elsewhere on the board
D3: D9.2 (A); also elsewhere on the board
GND: R33.1, R34.1, R35.1, R36.1; also elsewhere on the board
unnamed: D6.1 (K), R33.2
unnamed: D7.1 (K), R34.2
unnamed: D8.1 (K), R35.2
unnamed: D9.1 (K), R36.2

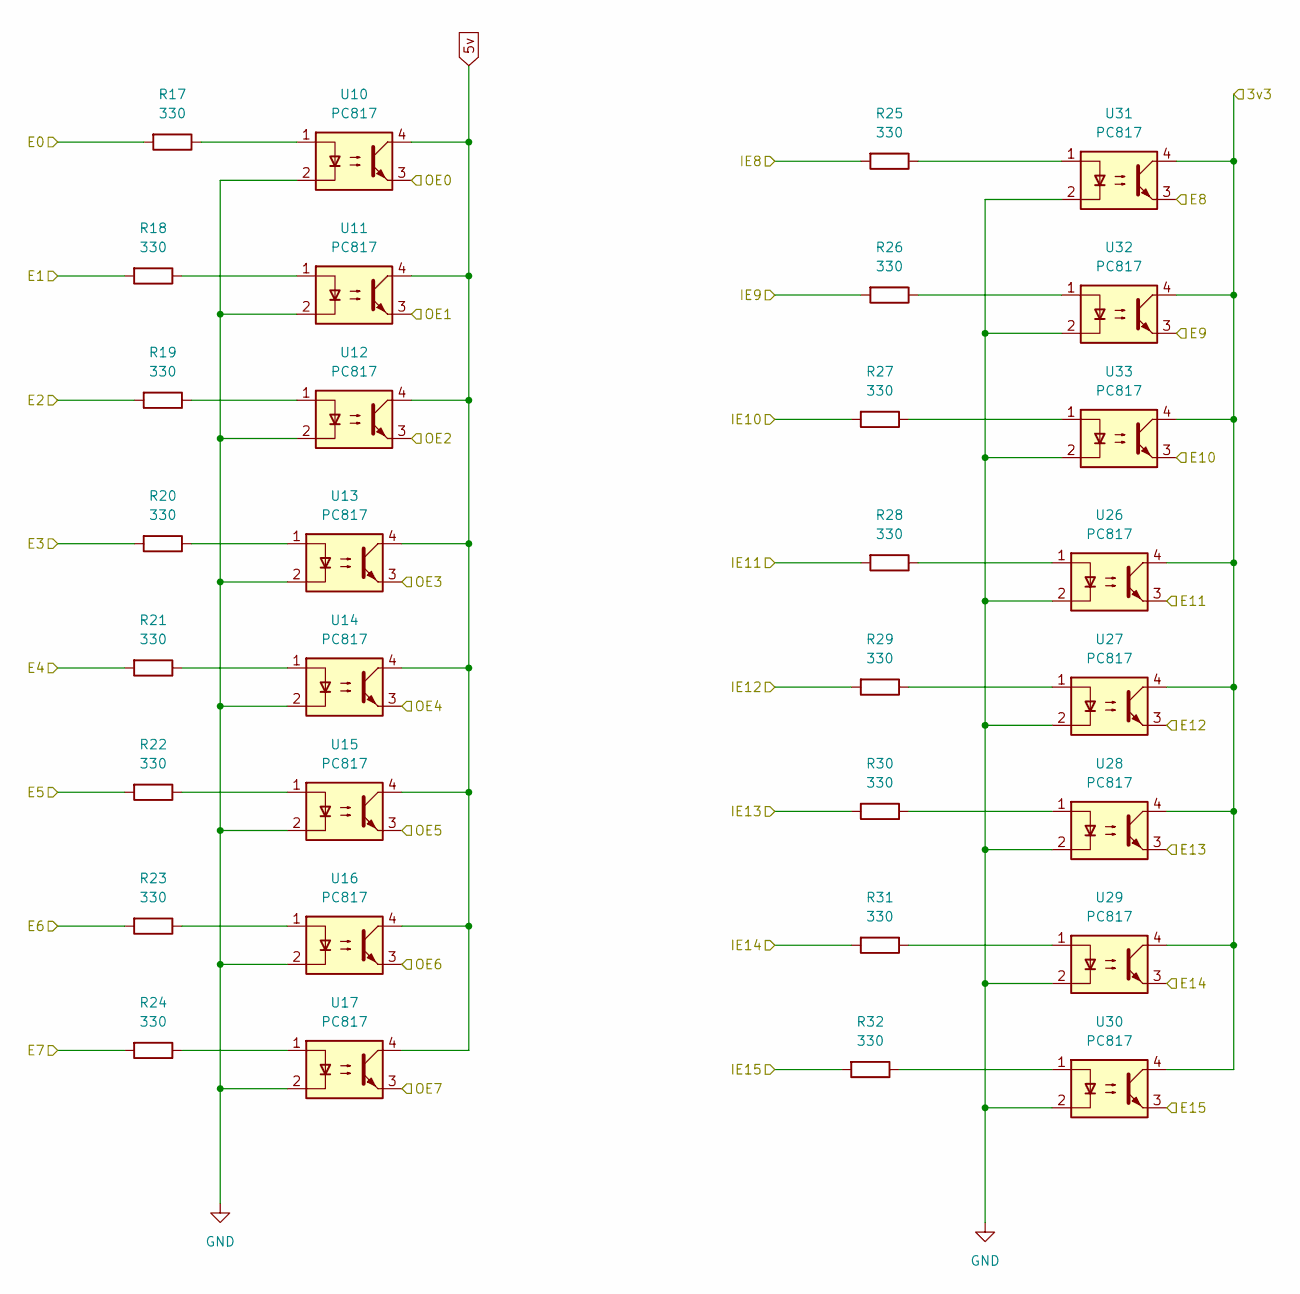
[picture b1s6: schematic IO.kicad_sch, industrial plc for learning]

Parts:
R17, R18, R19, R20, R21, R22, R23, R24, R25, R26, R27, R28, R29, R30, R31, R32: 330; R_0805_2012Metric_Pad1.20x1.40mm_HandSolder
U10, U11, U12, U13, U14, U15, U16, U17, U26, U27, U28, U29, U30, U31, U32, U33: PC817; DIP-4_W7.62mm

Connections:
3v3-LDO1: U26.4, U27.4, U28.4, U29.4, U30.4, U31.4, U32.4, U33.4; also elsewhere on the board
5v: U10.4, U11.4, U12.4, U13.4, U14.4, U15.4, U16.4, U17.4; also elsewhere on the board
/f4/IO/IE8: R25.2; also elsewhere on the board
/f4/IO/IE9: R26.2; also elsewhere on the board
/f4/IO/IE10: R27.2; also elsewhere on the board
/f4/IO/IE11: R28.2; also elsewhere on the board
/f4/IO/IE12: R29.2; also elsewhere on the board
/f4/IO/IE13: R30.2; also elsewhere on the board
/f4/IO/IE14: R31.2; also elsewhere on the board
/f4/IO/IE15: R32.2; also elsewhere on the board
/f4/IO/OE0: U10.3; also elsewhere on the board
/f4/IO/OE1: U11.3; also elsewhere on the board
/f4/IO/OE2: U12.3; also elsewhere on the board
/f4/IO/OE3: U13.3; also elsewhere on the board
/f4/IO/OE4: U14.3; also elsewhere on the board
/f4/IO/OE5: U15.3; also elsewhere on the board
/f4/IO/OE6: U16.3; also elsewhere on the board
/f4/IO/OE7: U17.3; also elsewhere on the board
E0: R17.2; also elsewhere on the board
E1: R18.2; also elsewhere on the board
E2: R19.2; also elsewhere on the board
E3: R20.2; also elsewhere on the board
E4: R21.2; also elsewhere on the board
E5: R22.2; also elsewhere on the board
E6: R23.2; also elsewhere on the board
E7: R24.2; also elsewhere on the board
E8: U31.3; also elsewhere on the board
E9: U32.3; also elsewhere on the board
E10: U33.3; also elsewhere on the board
E11: U26.3; also elsewhere on the board
E12: U27.3; also elsewhere on the board
E13: U28.3; also elsewhere on the board
E14: U29.3; also elsewhere on the board
E15: U30.3; also elsewhere on the board
GND: U10.2, U11.2, U12.2, U13.2, U14.2, U15.2, U16.2, U17.2, U26.2, U27.2, U28.2, U29.2, U30.2, U31.2, U32.2, U33.2; also elsewhere on the board
unnamed: R17.1, U10.1
unnamed: R18.1, U11.1
unnamed: R19.1, U12.1
unnamed: R20.1, U13.1
unnamed: R21.1, U14.1
unnamed: R22.1, U15.1
unnamed: R23.1, U16.1
unnamed: R24.1, U17.1
unnamed: R25.1, U31.1
unnamed: R26.1, U32.1
unnamed: R27.1, U33.1
unnamed: R28.1, U26.1
unnamed: R29.1, U27.1
unnamed: R30.1, U28.1
unnamed: R31.1, U29.1
unnamed: R32.1, U30.1
